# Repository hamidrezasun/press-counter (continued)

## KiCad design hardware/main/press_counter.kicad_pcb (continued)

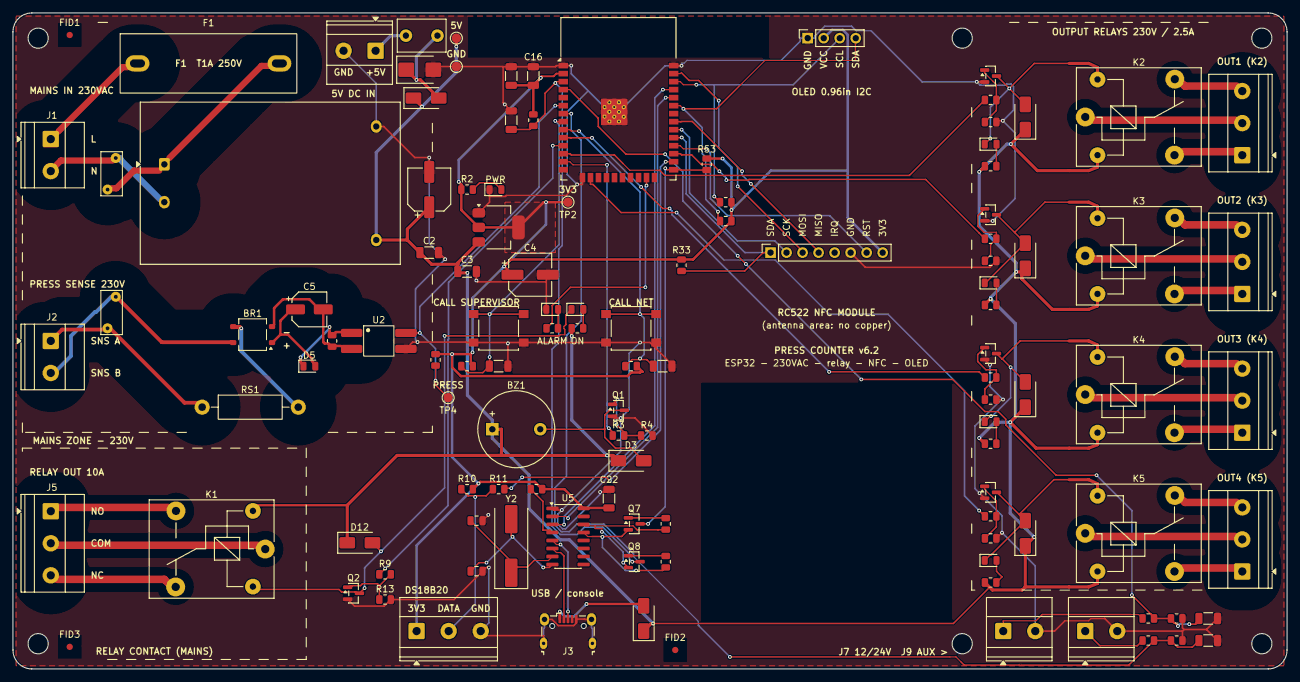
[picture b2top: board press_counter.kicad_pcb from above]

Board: 2 copper layers, 202.0 x 104.0 mm, 124 parts (0 on the bottom side), 85 nets.

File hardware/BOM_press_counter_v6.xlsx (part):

Hydraulic press counter v6.2 - BOM (one board + plug-in modules) | prices read 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
# | Designators | Qty on boards | Qty to buy (incl. spares) | Part / value | Footprint | Store | Shop product name | Unit price (Rial) | Unit price (Toman) | Line total (Toman) | Stock when checked | Buy link | Notes / alternative
1 | J1, J6, J2, J7, J9 | 5 | 5 | Screw terminal 2-pin 5.08 mm | TerminalBlock_Phoenix_MKDS-1,5-2-5.08_1x02_P5.08mm_Horizontal | eca.ir | ترمینال پیچی KF128-2Pin (5.08mm) | 190000 | 19000 | 95000 | in stock (checked 2026-10-19), min. order 5 | open page
2 | F1 | 1 | 5 | Fuse holder 5x20 PCB, covered (BLX-A type, 22.5 mm) | FuseHolder_5x20_PCB_P22.5 | eca.ir | BLX-A FUSE جافیوزی درب دار لولایی (PCB, with cover, for 5x20 glass fuse) | 98800 | 9880 | 49400 | in stock (checked 2026-10-19), min. order 5 | open page | Product id 1016 in the category 'جا فیوزی'. Pin pitch must be 22.5 mm +-0.5 (sl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
3 | RV1, RV2 | 2 | 5 | Varistor 07D471K (275 VAC) | RV_Disc_D7mm_W3.4mm_P5mm | eca.ir | وریستور VDR 07D471K | 59800 | 5980 | 29900 | in stock (checked 2026-10-19), min. order 5 | open page
4 | PS1 | 1 | 1 | AC-DC module 5V 1A (Hi-Link HLK-5M05) | Converter_ACDC_Hi-Link_HLK-5Mxx | javanelec.com | HLK-5M05 Hi-Link (مبدل 220 ولت AC به 5 ولت DC 1 آمپر) | 6493000 | 649300 | 649300 | in stock (add-to-cart, 2026-10-19) | open page | eca.ir (684,000) was out of stock on 2026-10-19. Other listings: leon (697,136)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
5 | C1 | 1 | 10 | SMD electrolytic 100uF 16V 6.3x5.4 | CP_Elec_6.3x5.4 | eca.ir | خازن SMD الکترولیت 100uF / 16V (6.3x5.4) | 71200 | 7120 | 71200 | in stock (checked 2026-10-19), min. order 10 | open page | Product id 3239.
6 | C2, C17, C22, C20, C23, C7, C8 | 7 | 50 | Capacitor 100nF 50V 1206 | C_1206_3216Metric | eca.ir | خازن 100nF پکیج SMD 1206 (50V) | 20000 | 2000 | 100000 | in stock (checked 2026-10-19), min. order 50 | open page
7 | F2 | 1 | 1 | Resettable fuse (PTC) 1.1A 60V radial | C_Disc_D7.5mm_W5.0mm_P5.00mm | voltatech.ir | فیوز برگشت پذیر PPTC RLD60P110XF 1.1A 60V | 80250 | 8025 | 8025 | in stock (2026-10-19) | open page | F2 on the 5 V terminal: radial resettable fuse, hold 1.1 A, 60 V, lead pitch 5.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
8 | D7 | 1 | 10 | TVS diode SMBJ6.5A unidirectional SMB | D_SMB | eca.ir | دیود TVS Unidirect پکیج SMB کد SMBJ6.5A | 44000 | 4400 | 44000 | in stock (checked 2026-10-19), min. order 10 | open page | D7 on the 5 V terminal (cathode band to +). SMBJ6.0A / SMBJ7.0A also fit; NOT S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
9 | D8, D14 | 2 | 20 | Schottky SS34 3A 40V SMA | D_SMA | eca.ir | دیود شاتکی 3A-40V مدل SS34 پکیج SMA | 23900 | 2390 | 47800 | in stock (checked 2026-10-19), min. order 20 | open page | D14 (USB) and D8 (5 V terminal). SS14 / SS24 (same SMA package) work too.
10 | U3 | 1 | 5 | LDO 3.3 V AMS1117 SOT-223 | SOT-223-3_TabPin2 | eca.ir | رگولاتور 3.3 ولت AMS1117 پکیج SOT-223 | 55700 | 5570 | 27850 | in stock (checked 2026-10-19), min. order 5 | open page
11 | C3, C16 | 2 | 50 | Capacitor 10uF 50V 1206 | C_1206_3216Metric | eca.ir | خازن 10uF پکیج SMD 1206 (50V) | 22800 | 2280 | 114000 | in stock (checked 2026-10-19), min. order 50 | open page | Product id 1691.
12 | C4 | 1 | 5 | SMD electrolytic 47uF 16V 6.3x5.4 | CP_Elec_6.3x5.4 | eca.ir | خازن SMD الکترولیت 47uF / 16V (6.3x5.4) | 74400 | 7440 | 37200 | in stock (checked 2026-10-19), min. order 5 | open page | Product id 2614.
13 | R2, R9, R43, R60, R80, R61, R81, R62, R82, R63, R83, R3 | 12 | 50 | Resistor 1k 0805 | R_0805_2012Metric | eca.ir | مقاومت 1K اهم SMD 0805 | 4570 | 457 | 22850 | in stock (checked 2026-10-19), min. order 50 | open page | Product id 3405.
14 | D6, D13 | 2 | 50 | LED 0805 green | LED_0805_2012Metric | eca.ir | SMD LED سبز پکیج 0805 | 7110 | 711 | 35550 | in stock (checked 2026-10-19), min. order 50 | open page
15 | K1, K2, K3, K4, K5 | 5 | 6 | Relay T73 SRD-05VDC-SL-C, 5 V coil, 10A 250VAC, SPDT | Relay_SPDT_SANYOU_SRD_Series_Form_C | robochip.ir | رله 5 ولت میلون (SPDT, T73 pin pattern; part code Relay-5V-Milon-SPDT-5A-240VAC) | 600000 | 60000 | 360000 | in stock (add-to-cart, price dated 1405-02) | open page | voltatech.ir has NO 5 V milon in stock (its 'milon 10 A' 5 V page is the HKF li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
16 | Q2, Q7, Q8, Q3, Q4, Q5, Q6, Q1 | 8 | 10 | NPN transistor SS8050 SOT-23 | SOT-23 | voltatech.ir | ترانزیستور SS8050 پکیج SMD | 10020 | 1002 | 10020 | in stock (2026-10-19) | open page | eca.ir (SOT-23) out of stock on 2026-10-19. javanelec.com 'SS8050' 1,050-1,870 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
17 | R13, R51, R53, R94, R95, R70, R71, R72, R73, R91, R99, R20, R21, R4, R33 | 15 | 50 | Resistor 10k 0805 | R_0805_2012Metric | eca.ir | مقاومت 10K اهم SMD 0805 | 8200 | 820 | 41000 | in stock (checked 2026-10-19), min. order 50 | open page | Product id 3411.
18 | D12, D20, D21, D22, D23, D3 | 6 | 50 | Diode 1N4007 SMD (M7) SMA | D_SMA | eca.ir | دیود 1N4007 SMD (M7) | 9970 | 997 | 49850 | in stock (checked 2026-10-19), min. order 50 | open page | voltatech.ir: 1,089 Toman.
19 | J5, J10, J11, J12, J13, J4 | 6 | 6 | Screw terminal 3-pin 5.08 mm | TerminalBlock_Phoenix_MKDS-1,5-3-5.08_1x03_P5.08mm_Horizontal | eca.ir | ترمینال پیچی KF128-3Pin (5.08mm) | 272000 | 27200 | 163200 | in stock (checked 2026-10-19), min. order 5 | open page
20 | RS1 | 1 | 25 | Resistor 120k 1W 5% axial (mains sense, through-hole) | R_Axial_DIN0411_L9.9mm_D3.6mm_P15.24mm_Horizontal | eca.ir | مقاومت 120K اهم 1W (axial, through-hole) | 21600 | 2160 | 54000 | in stock (checked 2026-10-19), min. order 25 | open page | Press-sense input RS1: one axial 120k 1 W resistor in the line leg (about 0.45 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
21 | BR1 | 1 | 5 | Bridge rectifier MB10S SOIC-4 | TO-269AA | eca.ir | پل دیود MB10S (SOIC-4, 1000V 0.5A) | 21100 | 2110 | 10550 | in stock (checked 2026-10-19), min. order 5 | open page
22 | C5 | 1 | 5 | SMD electrolytic 22uF 35V 5x5 | CP_Elec_5x5.4 | eca.ir | خازن SMD الکترولیت 22uF / 35V (5x5) | 69800 | 6980 | 34900 | in stock (checked 2026-10-19), min. order 5 | open page | Product id 13835.
23 | D5, D2 | 2 | 50 | LED 0805 red | LED_0805_2012Metric | eca.ir | SMD LED قرمز پکیج 0805 | 7110 | 711 | 35550 | in stock (checked 2026-10-19), min. order 50 | open page
24 | U2 | 1 | 1 | Optocoupler PC817 SMD SOP-4 | SOP4_Wide_Universal | voltatech.ir | اپتوکوپلر PC817 پکیج SMD | 85840 | 8584 | 8584 | in stock (2026-10-19) | open page | eca.ir out of stock on 2026-10-19. Footprint 'SOP4_Wide_Universal' covers wide 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
25 | R12, R40, R41, R10 | 4 | 50 | Resistor 2.2k 0805 | R_0805_2012Metric | eca.ir | مقاومت 2.2K اهم SMD 0805 | 4570 | 457 | 22850 | in stock (checked 2026-10-19), min. order 50 | open page | Product id 3408 (check that it is 2.2k, not 22k). I2C and 1-wire pull-ups.
26 | R1 | 1 | 50 | Resistor 22k 0805 | R_0805_2012Metric | eca.ir | مقاومت 22K اهم SMD 0805 | 4570 | 457 | 22850 | in stock (checked 2026-10-19), min. order 50 | open page | R1, pull-up of the press input IO34 (value chosen by SPICE, see hardware/sim). 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
27 | U1 | 1 | 1 | ESP32-WROOM-32 module (4 MB flash, PCB antenna) | ESP32-WROOM-32_Via03 | voltatech.ir | ماژول وایفای و بلوتوث ESP32-WROOM-32 | 6300000 | 630000 | 630000 | in stock (2026-10-19) | open page | ESP32-WROOM-32D / -32E fit the same footprint (4 MB flash needed); for a metal 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
28 | C18 | 1 | 50 | Capacitor 1uF 1206 | C_1206_3216Metric | eca.ir | خازن 1uF پکیج SMD 1206 (50V) | 27500 | 2750 | 137500 | in stock (checked 2026-10-19), min. order 50 | open page
29 | J3 | 1 | 1 | Micro-USB B receptacle SMD | USB_Micro-B_Wuerth_629105150521 | voltatech.ir | کانکتور Micro USB مادگی مدل SMD | 80220 | 8022 | 8022 | in stock (2026-10-19) | open page | eca.ir (85,200 Rial) out of stock on 2026-10-19. Footprint is the Wuerth 629105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
30 | U5 | 1 | 1 | USB-UART bridge CH340G SOP-16 | SOIC-16_3.9x9.9mm_P1.27mm | javanelec.com | CH340G (SOP-16) Nanjing Qinheng | 800000 | 80000 | 80000 | in stock (add-to-cart, 2026-10-19) | open page | eca.ir (93,600) out of stock on 2026-10-19. Other listings: Atrin 87,300, Moham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

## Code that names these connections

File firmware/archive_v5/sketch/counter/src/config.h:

// config.h - pin map and tunables of the counter node (bare STM32F103C8T6 on the v5 MAIN board).
// The nets are named in hardware/tools/design.py (main_board); the panel cable pin map is design.HMI_PINS.
#ifndef CONFIG_H
#define CONFIG_H

#include <Arduino.h>
#include "pc_proto.h"

// ── pins (STM32 pin names) ───────────────────────────────────────────────────────────────────────
// panel cable (J6): buttons are active LOW with the internal pull-up (1k series resistor on the main board, 100nF on the panel)
#define PIN_BTN_UP       PA0
#define PIN_BTN_DOWN     PA1
#define PIN_BTN_LEFT     PB4
#define PIN_BTN_RIGHT    PB5
#define PIN_BTN_OK       PB10
#define PIN_BTN_SUP      PB3    // CALL SUPERVISOR
#define PIN_BTN_NET      PA15   // CALL NET / MAINTENANCE
#define PIN_TFT_CS       PA4    // SPI1: SCK PA5, MISO PA6, MOSI PA7 (100R series resistors on SCK / MOSI)
#define PIN_TFT_DC       PB14
#define PIN_TFT_RST      PB15
#define PIN_TFT_BL       PB0    // TIM3_CH3 PWM back-light
#define PIN_RC_SS        PB12   // RC522 SDA/SS
#define PIN_RC_RST       PB13
#define PIN_LED_RUN      PB8    // panel, green: machine enabled (470 R on the panel board)
#define PIN_LED_ALERT    PB9    // panel, red: error / call
#define PIN_BUZZER       PA8    // panel: -> SS8050 -> 5 V buzzer, HIGH = on
// main board
#define PIN_PRESS        PB6    // PC817 output, 10k pull-up, LOW = press voltage present (EXTI6)
#define PIN_RELAY        PB7    // -> 1k -> SS8050 -> relay K1 coil, HIGH = relay closed = machine enabled; 10k pull-down while booting
#define PIN_TEMP         PB1    // LM35 via 1k + 100nF (ADC1_IN9)
// output relays OUT1..OUT4 (K2..K5): PB11, PC13, PC14, PC15 (see OUT_PINS in outputs.cpp; PC13-15 may only drive 3 mA: 2.2 k base resistors)
// voltage sense on ADC2 (sense.cpp): PA2 = 12 V input (divider 33k / 10k), PA3 = 230 V AC from a ZMPT101B module
// USART1 (PA9 TX / PA10 RX): link to the ESP8266 gateway.   USB (console): PA11 / PA12.   SWD: PA13 / PA14.
// BOOT1 = PB2 (strapped low, do not use).   No unused pins are left.

#define LINK_BAUD        38400UL

// ── display: 2.4in ST7789 module, 240 x 320, driven by display.cpp (no Adafruit libraries) ───────────
#ifndef DISPLAY_NATIVE_W
#define DISPLAY_NATIVE_W 240         // panel as delivered (portrait)
#define DISPLAY_NATIVE_H 320
#endif
#ifndef DISPLAY_MADCTL
#define DISPLAY_MADCTL   0xA0        // memory access control: MY | MV = landscape 320 x 240, RGB order (0x08 = BGR: use it if red and blue are swapped)
#endif
#ifndef DISPLAY_INVERT
#define DISPLAY_INVERT   1           // IPS panels need display inversion; set 0 if the colours look negative
#endif
#ifndef DISPLAY_SPI_HZ
#define DISPLAY_SPI_HZ   9000000UL   // 100 R series resistors + a ribbon cable: 9 MHz is safe, the panel could do 60 MHz
#endif

// ── timing / behaviour ───────────────────────────────────────────────────────────────────────────
#define BTN_DEBOUNCE_MS          25UL
#define BTN_LONG_MS              900UL
#define BTN_REPEAT_MS            180UL
#define BTN_CANCEL_CALL_MS       1500UL
#define TAG_COOLDOWN_MS          3000UL        // ignore the same card for 3 s after it was handled
#define TAG_WRITE_TIMEOUT_MS     30000UL
#define NFC_POLL_MS              150UL
#define NFC_HEALTH_MS            5000UL
#define TEMP_SAMPLE_MS           500UL
#define TEMP_REPORT_MS           60000UL
#define PRESS_GAP_MS             3UL           // an inactive gap shorter than this inside a pulse is contact bounce
#define PRESS_TRAIN_GAP_MS       1000UL
#define LINK_ALIVE_MS            6000UL        // gateway counts as present if it spoke within this time
#define LINK_ERROR_MS            30000UL       // ... and raises E05 after this long
#define SERVER_ERROR_MS          300000UL      // no WiFi for 5 minutes -> E06
#define STATUS_PERIOD_MS         1000UL        // status snapshot to the gateway
#define EVENT_RETRY_MS           2500UL
#define IWDG_TIMEOUT_MS          4000UL
#define UI_REFRESH_MS            250UL
#define BACKLIGHT_DIM_MS         120000UL      // dim the display after 2 minutes without button / tag
#define LIFETIME_SAVE_EVERY      25UL

#define MAX_TAG_TEXT             38            // fits the three data blocks of one MIFARE Classic sector
#define EVENT_QUEUE_SIZE         48
#define NAME_LEN                 24
#define LINE_PAYLOAD             200           // a link line payload

// ── hardware options ─────────────────────────────────────────────────────────────────────────────
#ifndef RELAY_ON_LEVEL
#define RELAY_ON_LEVEL HIGH
#endif

// Settings + lifetime counter live in the last two 1 KB pages of the first 64 KB (valid on every F103C8/CB).
#define STORE_SETTINGS_ADDR      0x0800F800UL
#define STORE_LOG_ADDR           0x0800FC00UL
#define STORE_PAGE_SIZE          1024UL

#endif  // CONFIG_H

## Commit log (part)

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2025-06-10 commit message
2025-06-12 renamed: press_counter_esp-01/V2.ino -> press_counter_esp-01/press_counter_esp-01.ino
2025-06-12 improvment
2025-06-18 this code work correctly but will fail if server not response because of no time out
2025-06-22 lastesst version of arduino code written using asyncHtppClient
2025-06-22 separate code into multiple files
2025-07-12 separate into multiple and using api error when using records in one day
2025-07-15 rfid not working
2025-07-15 rfid workingggggggggggggggggg
2025-07-16 end of arduino code
2025-08-21 test
2025-08-21 fixed
2025-09-03 bug in buzzer and PressCounter
2025-09-03 work correctly
2025-09-09 working with attachInterrupt
2025-09-16 correctly working
2025-09-20 improvement
